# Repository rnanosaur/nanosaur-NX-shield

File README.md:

# :sauropod: 🦸 nanosaur-NX-shield - [![CC BY-NC-SA 4.0][cc-by-nc-sa-image]][cc-by-nc-sa]

**nanosaur** The smallest [NVIDIA Jetson](https://developer.nvidia.com/buy-jetson) dinosaur robot, **open-source**, fully **3D printable**, based on [**ROS2**](https://www.ros.org/) & [**Isaac ROS**](https://developer.nvidia.com/isaac-ros-gems).

<small>Designed & made by [Raffaello Bonghi](https://rnext.it)</small>

Meet nanosaur:
* 🦕 Website: [nanosaur.ai](https://nanosaur.ai)
* 🦄 Do you need an help? [Discord](https://discord.gg/YvxjxEFPkb)
* 🧰 For technical details follow [wiki](https://github.com/rnanosaur/nanosaur/wiki)
* 🐳 nanosaur [Docker hub](https://hub.docker.com/u/nanosaur)
* ⁉️ Something wrong? Open an [issue](https://github.com/rnanosaur/nanosaur/issues)

# How make Nanosaur PCBs on PCBWay

- Register to PCBWay using [my refferer link](https://www.pcbway.com/setinvite.aspx?inviteid=472567)
- and ... **Work in progress!**

# Board design

This board is a simple adapter to connect the motor controller and the LCDs to the NVIDIA Jetson on your NanoSaur, this board connect:

* I2C bus 0 (Pin 27, 28)
  * oled right
  * IMU
* I2C bus 1 (Pin 3, 5)
  * oled left
  * adafruit motor control
  * USB [STUSB4500QTR](https://www.st.com/resource/en/datasheet/stusb4500.pdf)
* 2 custom LEDS
  * GPIO Pin 31
  * GPIO Pin 33

## NVIDIA Jetson Reference

* Jetsonhacks [Jetson Xavier NX pinout](https://www.jetsonhacks.com/nvidia-jetson-xavier-nx-gpio-header-pinout/)
* Jetsonhacks [Jetson Nano pinout](https://www.jetsonhacks.com/nvidia-jetson-nano-j41-header-pinout/)

## STUSB4500QTR

* [STUSB4500QTR](https://www.st.com/en/interfaces-and-transceivers/stusb4500.html)
* [Evaluation board EVAL-SCS001V1](https://www.st.com/content/st_com/en/products/evaluation-tools/solution-evaluation-tools/psu-and-converter-solution-eval-boards/eval-scs001v1.html)
* [ST Easy migration](https://www.st.com/resource/en/user_manual/um2586-fast-and-easy-migration-from-dc-barrel-to-typec-stmicroelectronics.pdf)
* [Github STUSB4500](https://github.com/usb-c/STUSB4500)
* [Sparkgun tutorial](https://learn.sparkfun.com/tutorials/power-delivery-board---usb-c-qwiic-hookup-guide)
* [Hackaday tutorial](https://hackaday.com/2019/10/18/usb-power-delivery-for-all-the-things/)
* [STM presentation](https://www.stmicroelectronics.com.cn/content/dam/AME/2019/technology-tour-2019/chicago/presentations/T1S3_Schaumburg_USB-Type-C_G.Gosciniak.pdf)

# Develop

The documentation is made using [Kicad](https://www.kicad.org/) 6

The CI is made using
* [Kibot](https://github.com/INTI-CMNB/KiBot)
* [kicad-exports](https://github.com/nerdyscout/kicad-exports)

# License

This project is under license [Creative Commons Attribution-NonCommercial-ShareAlike 4.0 International License][cc-by-nc-sa].

[cc-by-nc-sa]: http://creativecommons.org/licenses/by-nc-sa/4.0/
[cc-by-nc-sa-image]: https://licensebuttons.net/l/by-nc-sa/4.0/88x31.png
[cc-by-nc-sa-shield]: https://img.shields.io/badge/License-CC%20BY--NC--SA%204.0-lightgrey.svg

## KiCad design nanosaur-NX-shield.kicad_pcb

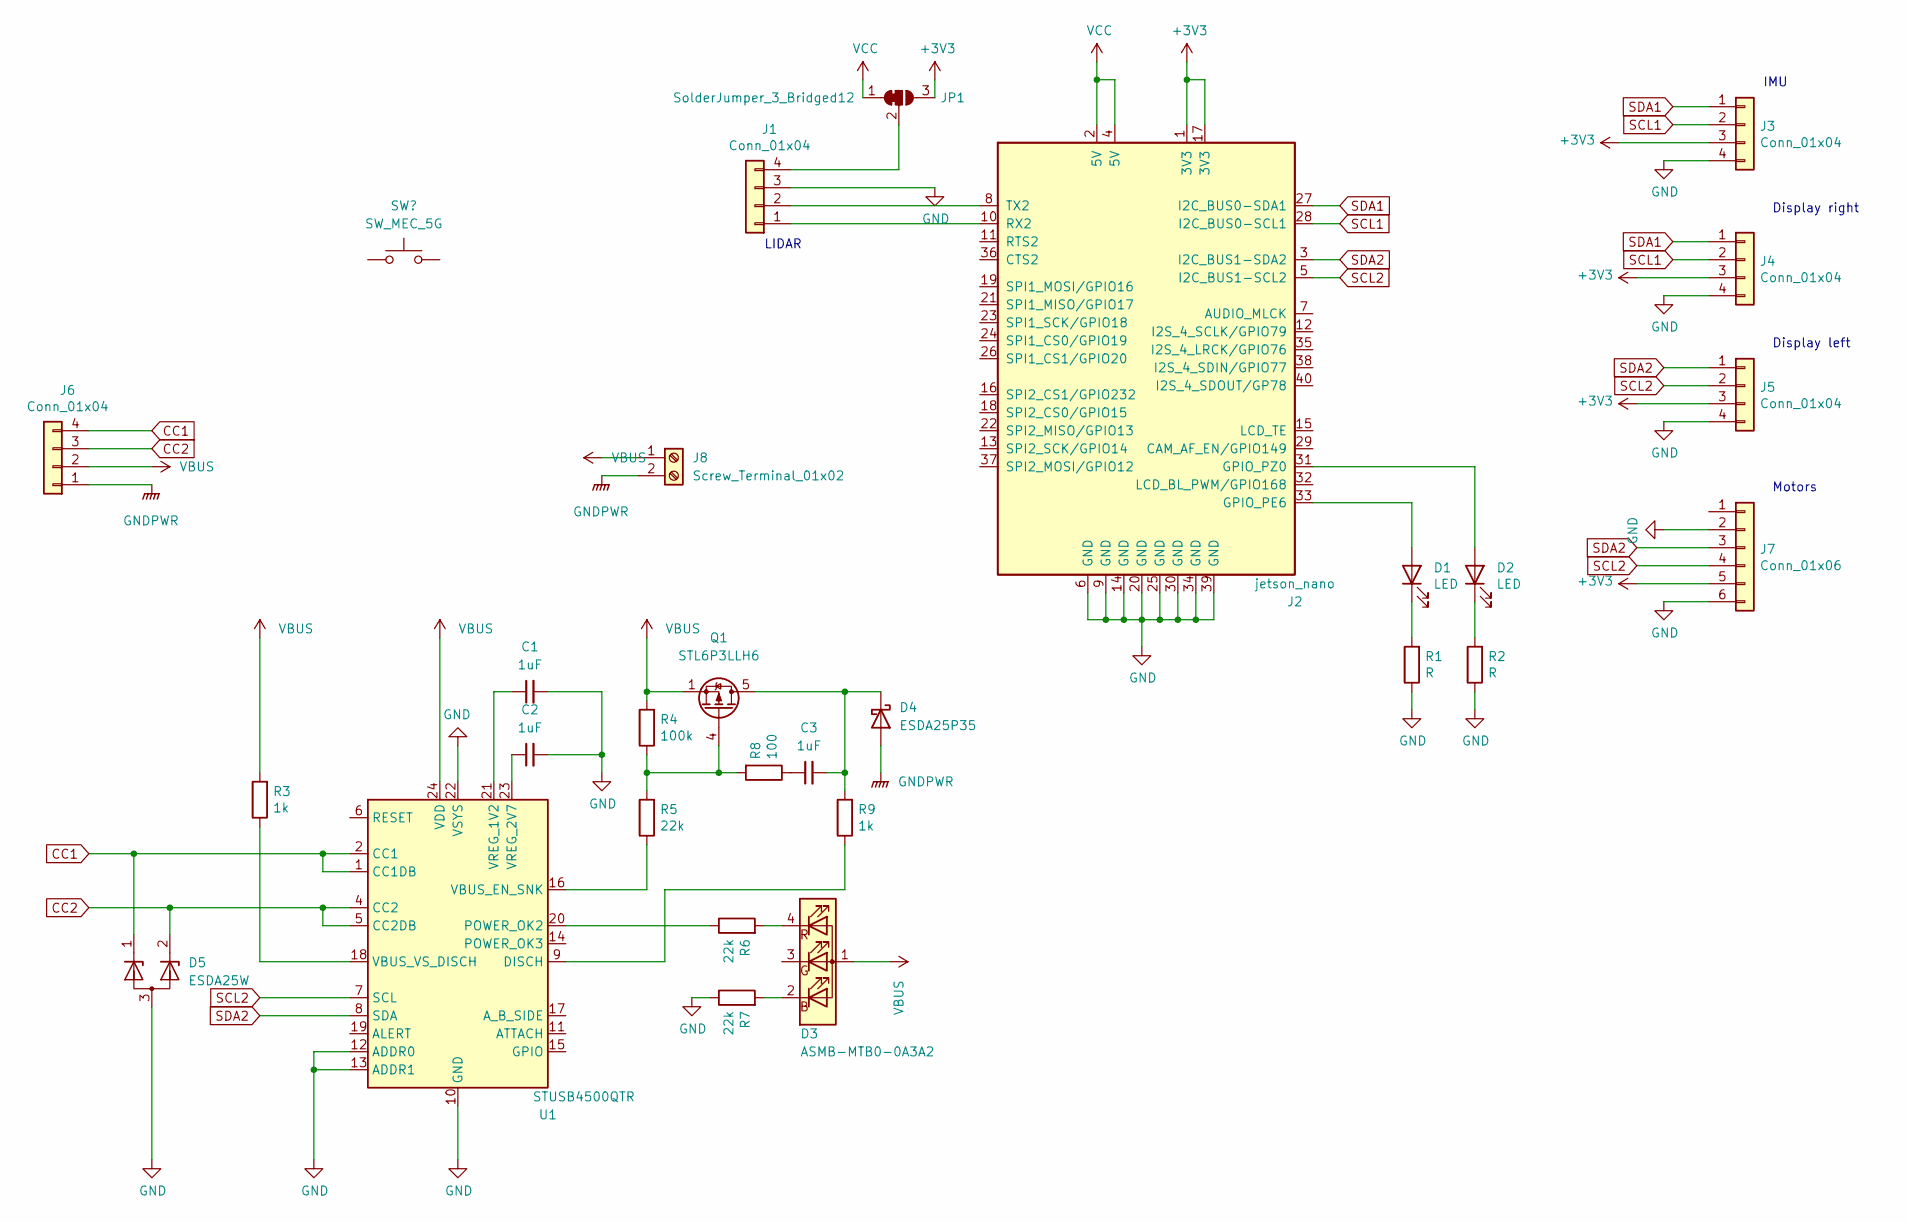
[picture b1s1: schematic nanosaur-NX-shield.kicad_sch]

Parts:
C1, C2, C3: 1uF; C_0603_1608Metric
D1, D2: LED; LED_D3.0mm_Horizontal_O1.27mm_Z2.0mm
D3: ASMB-MTB0-0A3A2; LED_Avago_PLCC4_3.2x2.8mm_CW
D4: ESDA25P35; D_MicroMELF
D5: ESDA25W; SOT-23
J1, J3, J4, J5, J6: Conn_01x04; PinHeader_1x04_P2.54mm_Vertical
J2: jetson_nano; PinHeader_2x20_P2.54mm_Vertical
J7: Conn_01x06; PinHeader_1x06_P2.54mm_Vertical
J8: Screw_Terminal_01x02; TerminalBlock_Phoenix_MPT-0,5-2-2.54_1x02_P2.54mm_Horizontal
JP1: SolderJumper_3_Bridged12; SolderJumper-3_P1.3mm_Bridged12_Pad1.0x1.5mm
Q1: STL6P3LLH6; PowerPAK_SO-8_Single
R1, R2: R; R_0603_1608Metric
R3, R9: 1k; R_0603_1608Metric
R4: 100k; R_0603_1608Metric
R5, R6, R7: 22k; R_0603_1608Metric
R8: 100; R_0603_1608Metric
U1: STUSB4500QTR; QFN-24-1EP_4x4mm_P0.5mm_EP2.7x2.7mm

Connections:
+3V3: J2.1 (3V3), J2.17 (3V3), J3.3, J4.3, J5.3, J7.5, JP1.3 (B)
CC1: D5.1 (K), J6.4, U1.1 (CC1DB), U1.2 (CC1)
CC2: D5.2 (K), J6.3, U1.4 (CC2), U1.5 (CC2DB)
GND: C1.2, C2.2, D5.3 (A), J1.3, J2.6 (GND), J2.9 (GND), J2.14 (GND), J2.20 (GND), J2.25 (GND), J2.30 (GND), J2.34 (GND), J2.39 (GND), J3.4, J4.4, J5.4, J7.2, J7.6, R1.1, R2.1, R7.1, U1.10 (GND), U1.12 (ADDR0), U1.13 (ADDR1), U1.22 (VSYS), U1.25 (GND)
GNDPWR: D4.2 (A), J6.1, J8.2
unnamed: C1.1, U1.21 (VREG_1V2)
unnamed: C2.1, U1.23 (VREG_2V7)
unnamed: C3.1, R8.1
unnamed: C3.2, D4.1 (K), Q1.5 (D), R9.2
unnamed: D1.1 (K), R1.2
unnamed: D1.2 (A), J2.33 (GPIO_PE6)
unnamed: D2.1 (K), R2.2
unnamed: D2.2 (A), J2.31 (GPIO_PZ0)
unnamed: D3.2 (BK), R7.2
unnamed: D3.4 (RK), R6.2
unnamed: J1.1, J2.10 (RX2)
unnamed: J1.2, J2.8 (TX2)
unnamed: J1.4, JP1.2 (C)
unnamed: Q1.4 (G), R4.1, R5.2, R8.2
unnamed: R3.1, U1.18 (VBUS_VS_DISCH)
unnamed: R5.1, U1.16 (VBUS_EN_SNK)
unnamed: R6.1, U1.20 (POWER_OK2)
unnamed: R9.1, U1.9 (DISCH)
SCL1: J2.28 (I2C_BUS0-SCL1), J3.2, J4.2
SCL2: J2.5 (I2C_BUS1-SCL2), J5.2, J7.4, U1.7 (SCL)
SDA1: J2.27 (I2C_BUS0-SDA1), J3.1, J4.1
SDA2: J2.3 (I2C_BUS1-SDA2), J5.1, J7.3, U1.8 (SDA)
VBUS: D3.1 (A), J6.2, J8.1, Q1.1 (S), Q1.2 (S), Q1.3 (S), R3.2, R4.2, U1.24 (VDD)
VCC: J2.2 (5V), J2.4 (5V), JP1.1 (A)

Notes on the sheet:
LIDAR
IMU
Motors
Display right
Display left

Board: 2 copper layers, 28 parts (2 on the bottom side), 29 nets, no tracks yet.

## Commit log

2021-10-16 Add kicad base project
2021-10-16 Fix dependabot
2022-02-07 Improve schematich
2022-02-12 Add PCB first draft
2022-07-24 Improve schematics and PCB
